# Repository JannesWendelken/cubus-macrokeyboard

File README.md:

# cubus-macrokeyboard
**Designed for comfort and efficiency when you're working at your computer.**

The **cubus-macrokeyboard** is a 4-key programmable macro pad created for the **HackClub Blueprint Event**. It's built with the **XIAO Seed RP2040** for maximum flexibility and ease of customization.

---

## Features:
- **4 Programmable Keys**  
  Customize each key for shortcuts, macros, or custom commands.
  
- **Powered by XIAO Seed RP2040**  
  A compact and powerful microcontroller ideal for small, customizable projects.

---

## Getting Started:
1. **Program the Keys**  
   Flash the XIAO RP2040 with your preferred firmware (e.g., CircuitPython, Arduino, or KMK).
   
2. **Customize the Macros**  
   Set up key functions for shortcuts, automation, or any actions that help improve your workflow.

---

## Hardware:
- **XIAO Seed RP2040** microcontroller
- **4 mechanical keys** (MX-style switches)
- **USB-C connection**

---

## License:
MIT License — free to use, modify, and share.

---

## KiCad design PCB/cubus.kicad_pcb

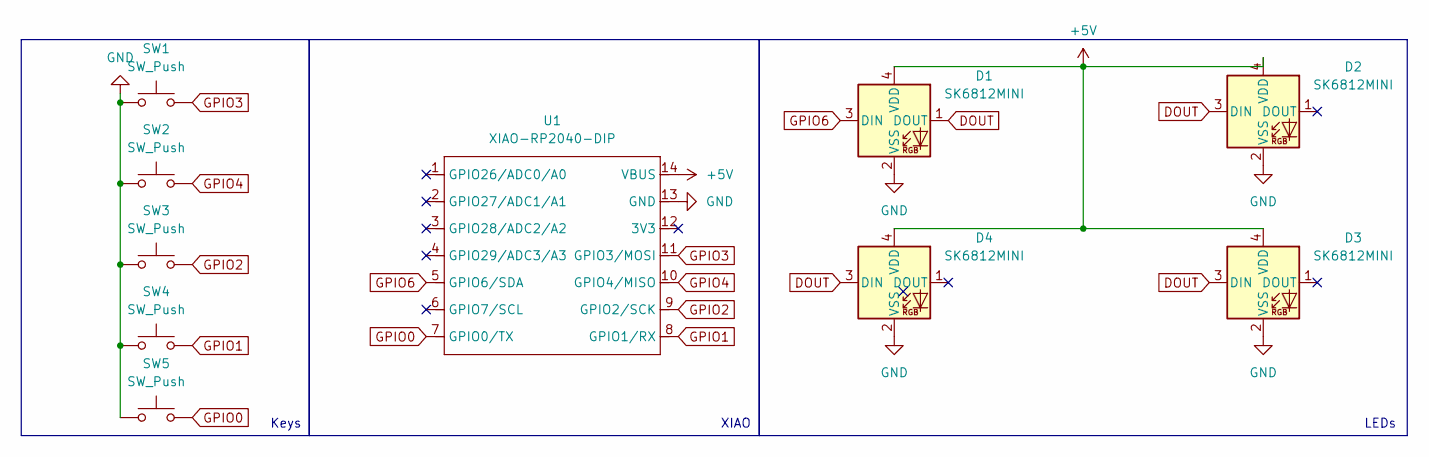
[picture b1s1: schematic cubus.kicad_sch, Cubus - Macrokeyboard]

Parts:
D1, D2, D3, D4: SK6812MINI; LED_SK6812MINI_PLCC4_3.5x3.5mm_P1.75mm
SW1, SW2, SW3, SW4, SW5: SW_Push; SW_Cherry_MX_1.00u_PCB
U1: XIAO-RP2040-DIP

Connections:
+5V: D1.4 (VDD), D2.4 (VDD), D3.4 (VDD), D4.4 (VDD), U1.14 (VBUS)
DOUT: D1.1 (DOUT), D2.3 (DIN), D3.3 (DIN), D4.3 (DIN)
GND: D1.2 (VSS), D2.2 (VSS), D3.2 (VSS), D4.2 (VSS), SW1.1, SW2.1, SW3.1, SW4.1, SW5.1, U1.13 (GND)
GPIO0: SW5.2, U1.7 (GPIO0/TX)
GPIO1: SW4.2, U1.8 (GPIO1/RX)
GPIO2: SW3.2, U1.9 (GPIO2/SCK)
GPIO3: SW1.2, U1.11 (GPIO3/MOSI)
GPIO4: SW2.2, U1.10 (GPIO4/MISO)
GPIO6: D1.3 (DIN), U1.5 (GPIO6/SDA)

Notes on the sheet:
XIAO
LEDs
Keys

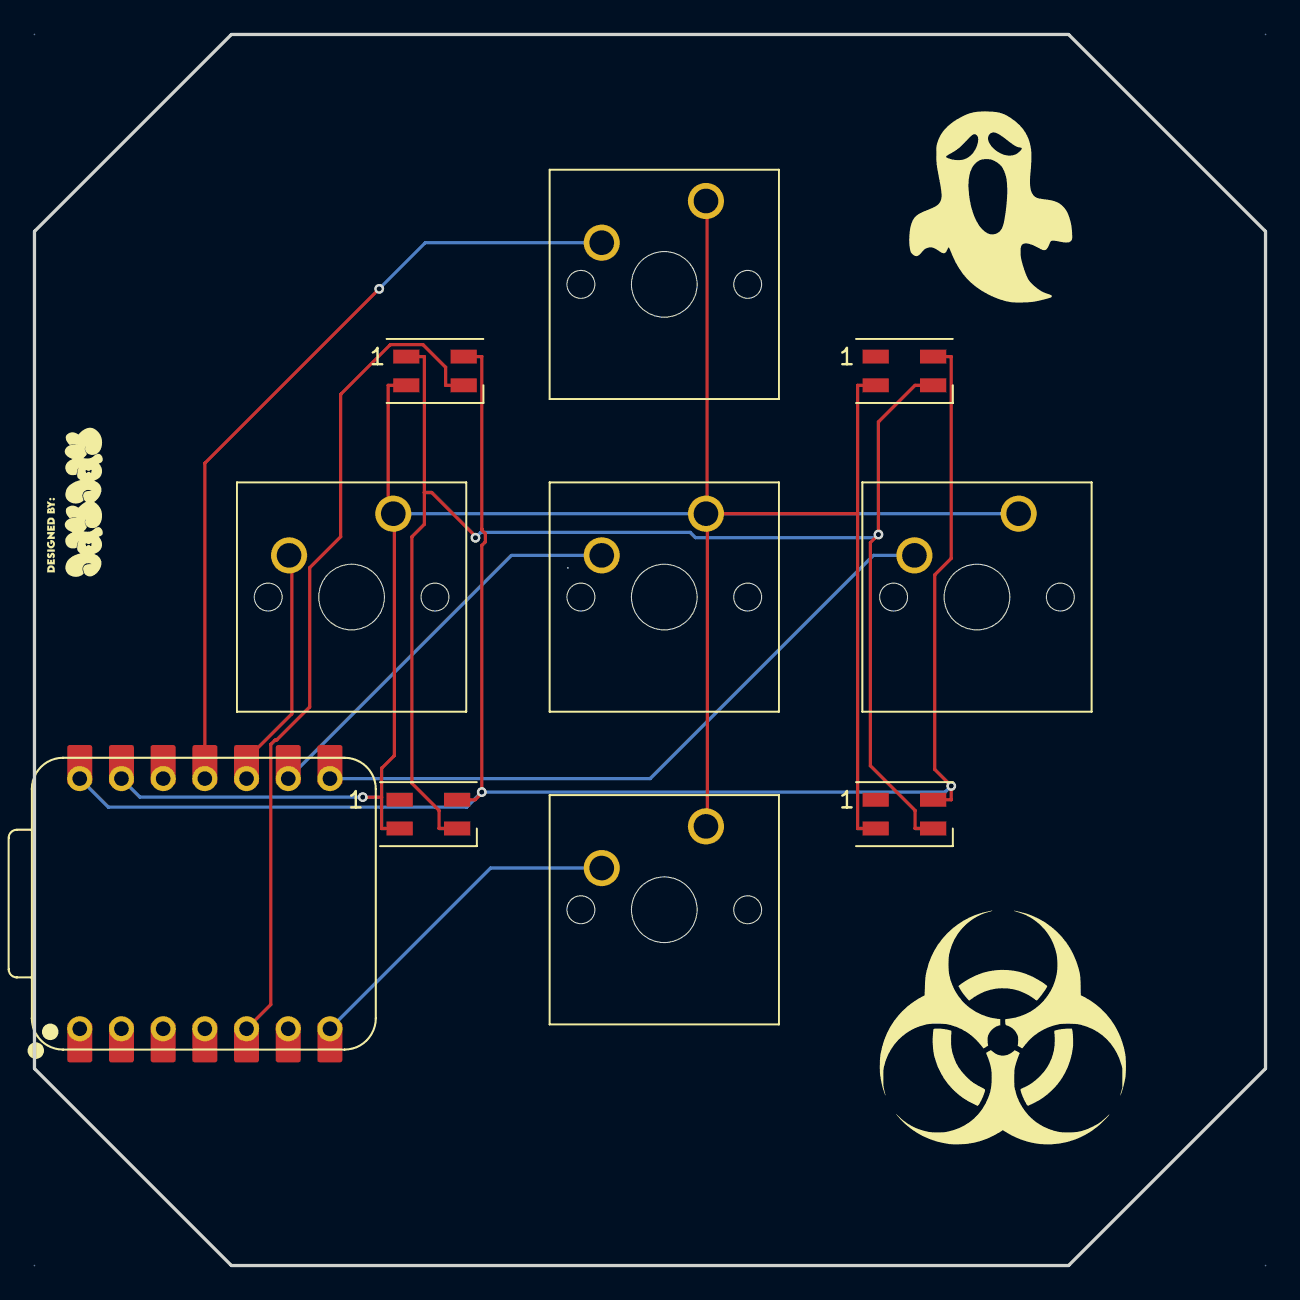
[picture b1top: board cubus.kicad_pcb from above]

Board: 2 copper layers, 75.0 x 75.0 mm, 10 parts (0 on the bottom side), 9 nets.

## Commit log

2025-12-03 Added Main Files
    Included the complete Prototype File Structure for my Project.
2025-12-03 Rename Macropad.kicad_pro to PCB/Macropad.kicad_pro
2025-12-03 Rename cubus_case.step to CAD/cubus_case.step
2025-12-09 updated files
2025-12-09 Rename cubus.kicad_pro to PCB/cubus.kicad_pro
2025-12-09 Rename cad.png to IMG/cad.png
